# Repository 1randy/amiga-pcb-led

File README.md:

# amiga-pcb-led
Amiga600 LED replacement PCB, Eagle 7.x Schematics & Board

## Schematic

## Board

## PCB

## License

GNU General Public License v3.0

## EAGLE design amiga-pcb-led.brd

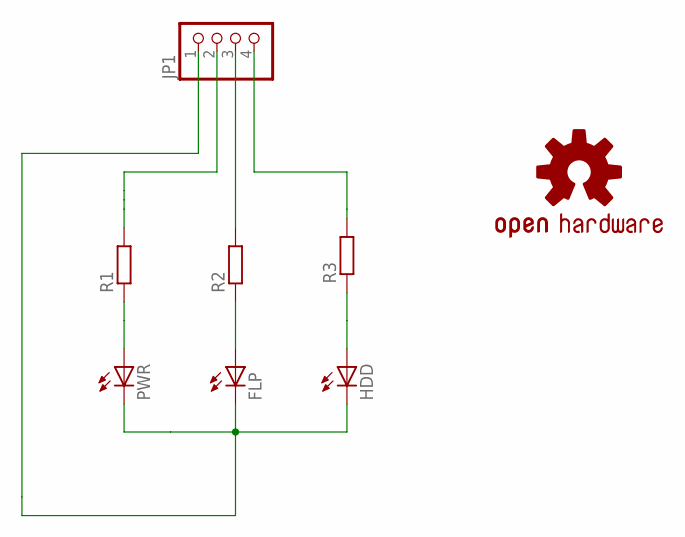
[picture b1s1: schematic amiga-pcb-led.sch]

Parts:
FLP: LEDSQR2X5; LED2X5
HDD: LEDSQR2X5; LED2X5
JP1: PINHD-1X4; 1X04
LOGO2: OSHW-LOGOS-COPPER; OSHW-LOGO-S_COPPER
PWR: LEDSQR2X5; LED2X5
R1, R2, R3: R-EU_R0603; R0603

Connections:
GND: FLP.K (C), HDD.K (C), JP1.1, PWR.K (C)
unnamed: PWR.A, R1.1
unnamed: FLP.A, R2.1
unnamed: HDD.A, R3.1
unnamed: JP1.2, R1.2
unnamed: JP1.3, R2.2
unnamed: JP1.4, R3.2

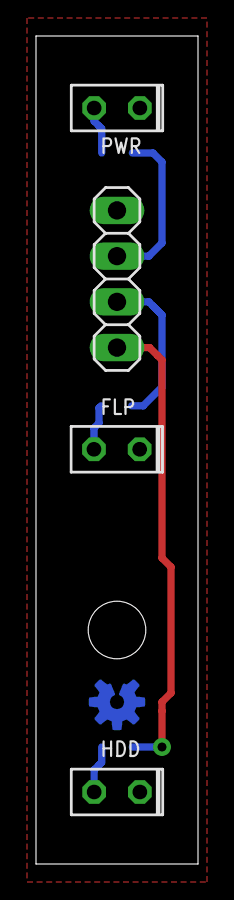
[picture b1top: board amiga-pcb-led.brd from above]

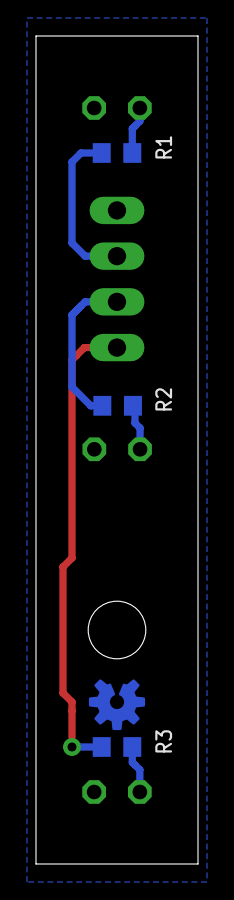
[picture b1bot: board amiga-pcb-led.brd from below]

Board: 2 copper layers, 9.0 x 46.0 mm, 8 parts (4 on the bottom side), 7 nets.

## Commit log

2018-10-24 inital upload

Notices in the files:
parts and their libraries:
SparkFun-Aesthetics: Licensing: Creative Commons ShareAlike 4.0 International - https://creativecommons.org/licenses/by-sa/4.0
